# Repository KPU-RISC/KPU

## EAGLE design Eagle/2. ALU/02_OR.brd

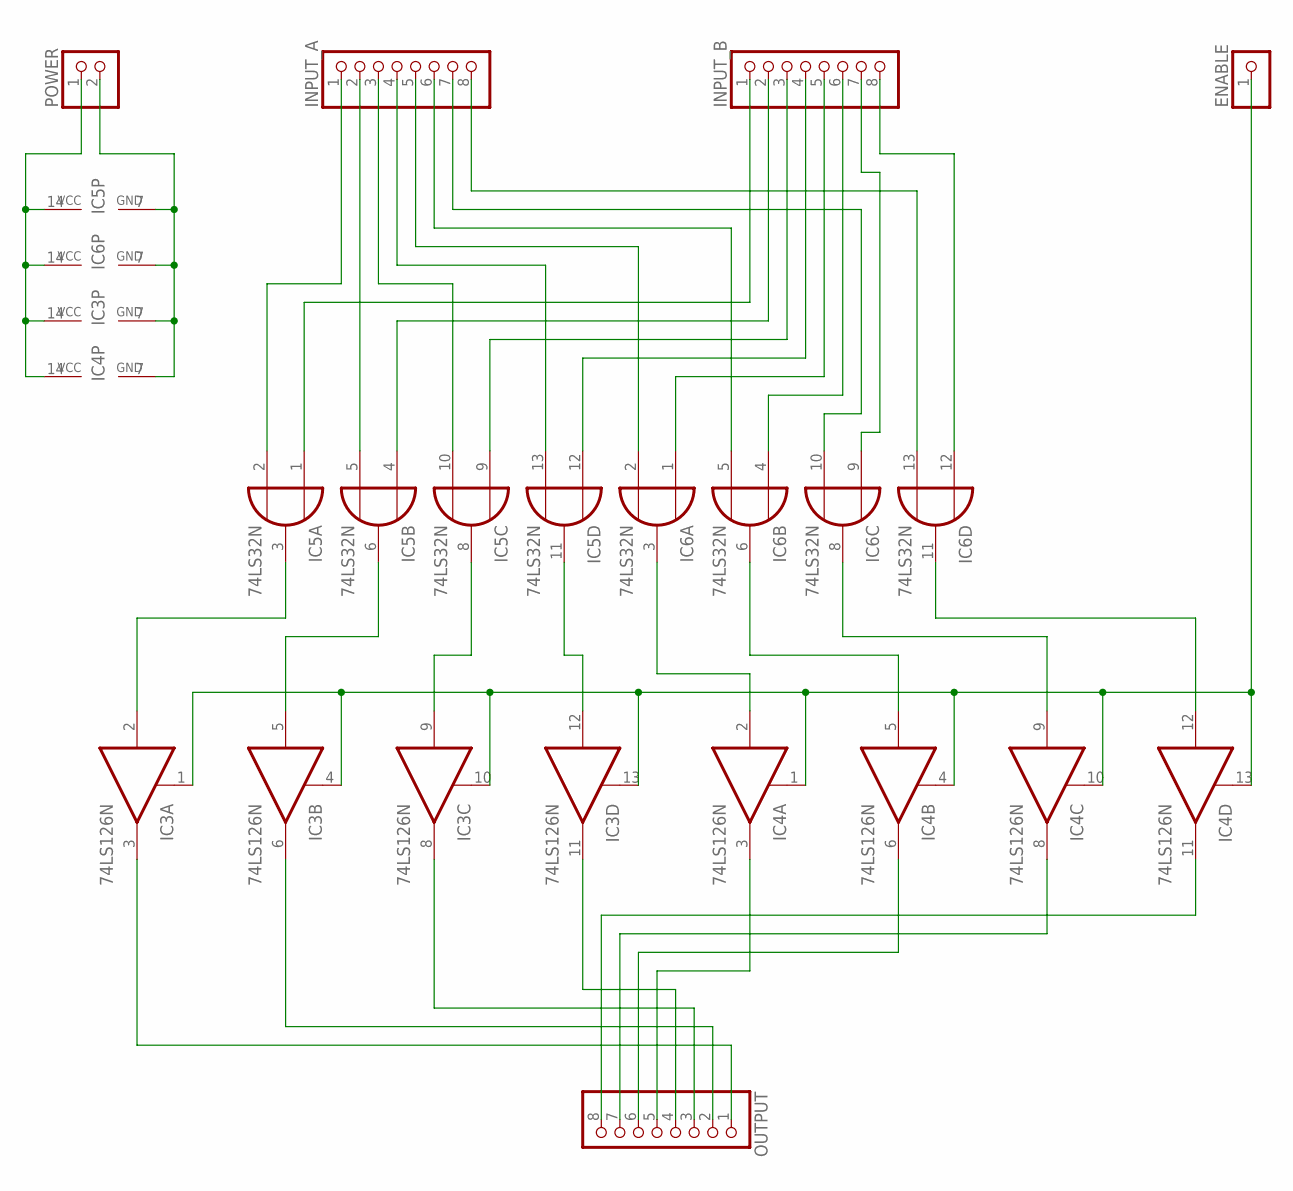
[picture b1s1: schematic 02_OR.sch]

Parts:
ENABLE: PINHD-1X1; 1X01
IC3, IC4: 74LS126N; DIL14
IC5, IC6: 74LS32N; DIL14
INPUT_A: PINHD-1X8; 1X08
INPUT_B: PINHD-1X8; 1X08
OUTPUT: PINHD-1X8; 1X08
POWER: PINHD-1X2; 1X02

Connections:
GND: IC3.7 (GND), IC4.7 (GND), IC5.7 (GND), IC6.7 (GND), POWER.2
unnamed: IC5.2 (I1), INPUT_A.1
unnamed: IC5.1 (I0), INPUT_B.1
unnamed: IC5.5 (I1), INPUT_A.2
unnamed: IC5.4 (I0), INPUT_B.2
unnamed: IC5.10 (I1), INPUT_A.3
unnamed: IC5.9 (I0), INPUT_B.3
unnamed: IC5.13 (I1), INPUT_A.4
unnamed: IC5.12 (I0), INPUT_B.4
unnamed: IC6.2 (I1), INPUT_A.5
unnamed: IC6.1 (I0), INPUT_B.5
unnamed: IC6.5 (I1), INPUT_A.6
unnamed: IC6.4 (I0), INPUT_B.6
unnamed: IC6.10 (I1), INPUT_A.7
unnamed: IC6.9 (I0), INPUT_B.7
unnamed: IC6.13 (I1), INPUT_A.8
unnamed: IC6.12 (I0), INPUT_B.8
unnamed: IC3.5 (I), IC5.6 (O)
unnamed: IC3.9 (I), IC5.8 (O)
unnamed: IC3.12 (I), IC5.11 (O)
unnamed: IC4.2 (I), IC6.3 (O)
unnamed: IC4.5 (I), IC6.6 (O)
unnamed: IC4.9 (I), IC6.8 (O)
unnamed: IC4.12 (I), IC6.11 (O)
unnamed: IC3.3 (O), OUTPUT.1
unnamed: IC3.6 (O), OUTPUT.2
unnamed: IC3.8 (O), OUTPUT.3
unnamed: IC3.11 (O), OUTPUT.4
unnamed: IC4.3 (O), OUTPUT.5
unnamed: IC4.6 (O), OUTPUT.6
unnamed: IC4.8 (O), OUTPUT.7
unnamed: IC4.11 (O), OUTPUT.8
unnamed: ENABLE.1, IC3.1 (OE), IC3.4 (OE), IC3.10 (OE), IC3.13 (OE), IC4.1 (OE), IC4.4 (OE), IC4.10 (OE), IC4.13 (OE)
unnamed: IC3.2 (I), IC5.3 (O)
VCC: IC3.14 (VCC), IC4.14 (VCC), IC5.14 (VCC), IC6.14 (VCC), POWER.1

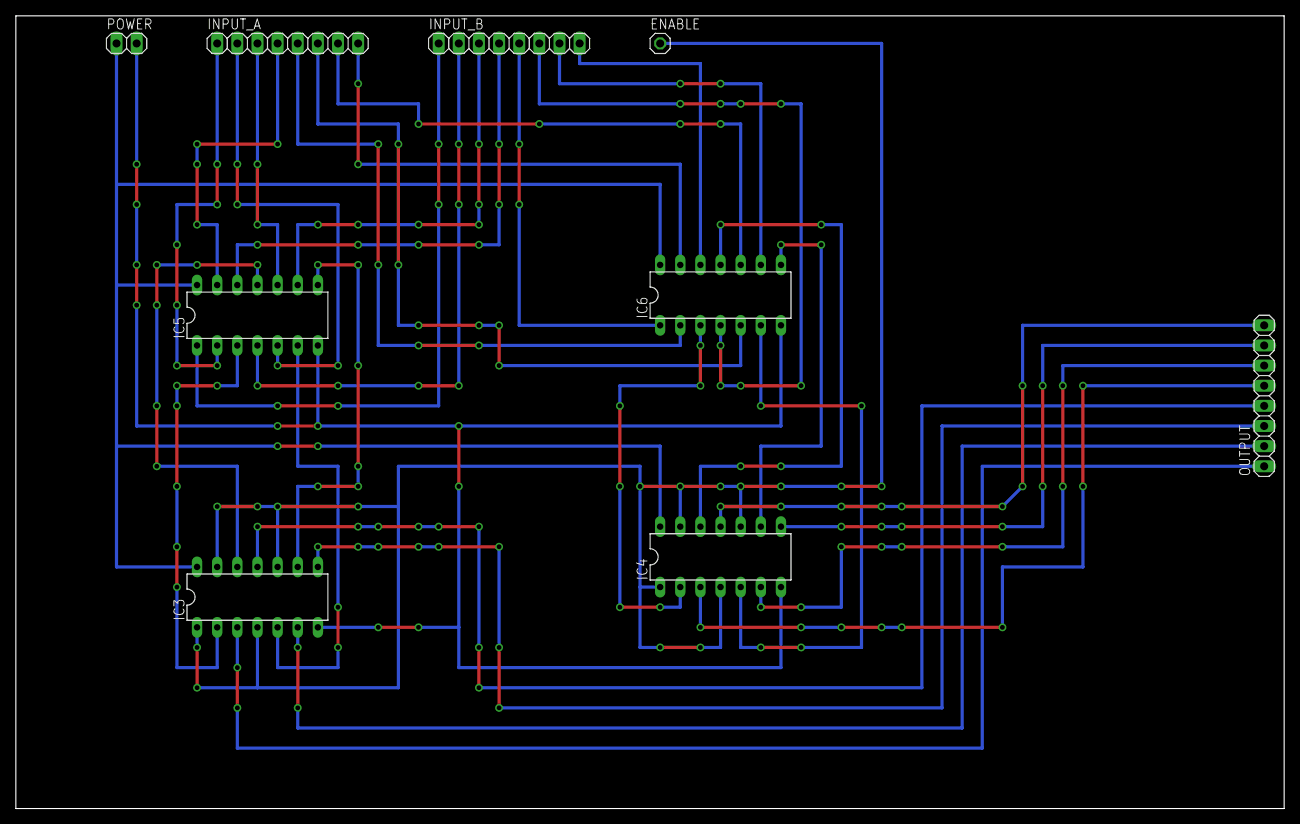
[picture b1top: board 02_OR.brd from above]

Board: 2 copper layers, 160.0 x 100.0 mm, 9 parts (0 on the bottom side), 35 nets.

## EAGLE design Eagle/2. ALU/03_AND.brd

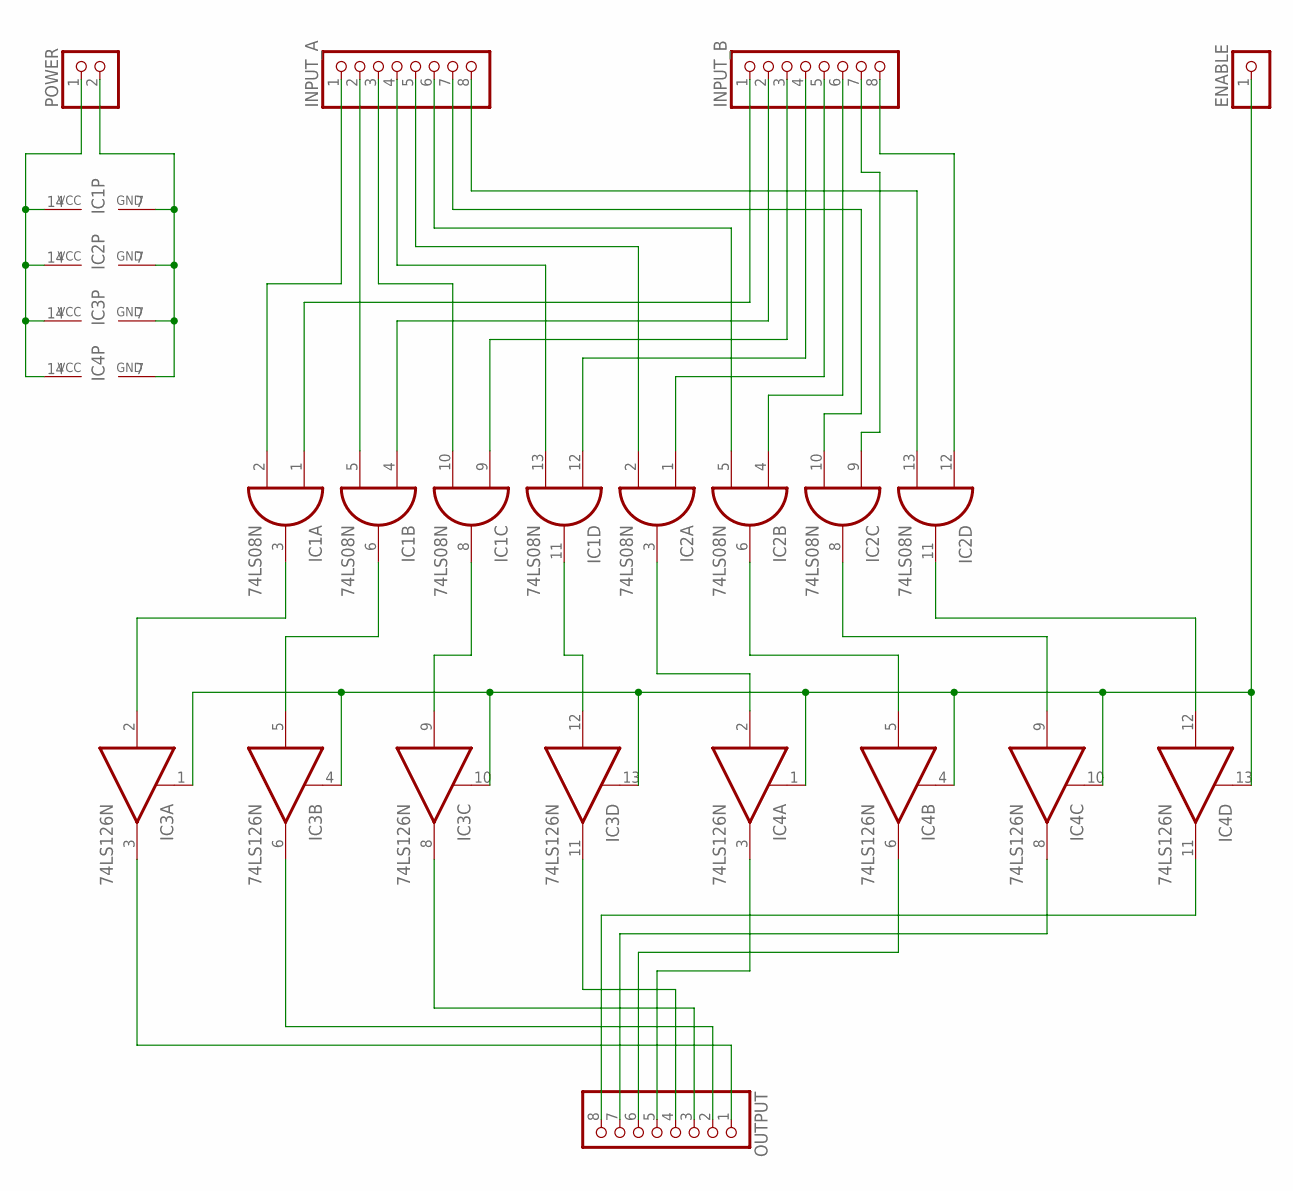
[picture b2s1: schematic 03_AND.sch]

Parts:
ENABLE: PINHD-1X1; 1X01
IC1, IC2: 74LS08N; DIL14
IC3, IC4: 74LS126N; DIL14
INPUT_A: PINHD-1X8; 1X08
INPUT_B: PINHD-1X8; 1X08
OUTPUT: PINHD-1X8; 1X08
POWER: PINHD-1X2; 1X02

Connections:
GND: IC1.7 (GND), IC2.7 (GND), IC3.7 (GND), IC4.7 (GND), POWER.2
unnamed: IC1.2 (I1), INPUT_A.1
unnamed: IC1.1 (I0), INPUT_B.1
unnamed: IC1.5 (I1), INPUT_A.2
unnamed: IC1.4 (I0), INPUT_B.2
unnamed: IC1.10 (I1), INPUT_A.3
unnamed: IC1.9 (I0), INPUT_B.3
unnamed: IC1.13 (I1), INPUT_A.4
unnamed: IC1.12 (I0), INPUT_B.4
unnamed: IC2.2 (I1), INPUT_A.5
unnamed: IC2.1 (I0), INPUT_B.5
unnamed: IC2.5 (I1), INPUT_A.6
unnamed: IC2.4 (I0), INPUT_B.6
unnamed: IC2.10 (I1), INPUT_A.7
unnamed: IC2.9 (I0), INPUT_B.7
unnamed: IC2.13 (I1), INPUT_A.8
unnamed: IC2.12 (I0), INPUT_B.8
unnamed: IC1.6 (O), IC3.5 (I)
unnamed: IC1.8 (O), IC3.9 (I)
unnamed: IC1.11 (O), IC3.12 (I)
unnamed: IC2.3 (O), IC4.2 (I)
unnamed: IC2.6 (O), IC4.5 (I)
unnamed: IC2.8 (O), IC4.9 (I)
unnamed: IC2.11 (O), IC4.12 (I)
unnamed: IC3.3 (O), OUTPUT.1
unnamed: IC3.6 (O), OUTPUT.2
unnamed: IC3.8 (O), OUTPUT.3
unnamed: IC3.11 (O), OUTPUT.4
unnamed: IC4.3 (O), OUTPUT.5
unnamed: IC4.6 (O), OUTPUT.6
unnamed: IC4.8 (O), OUTPUT.7
unnamed: IC4.11 (O), OUTPUT.8
unnamed: ENABLE.1, IC3.1 (OE), IC3.4 (OE), IC3.10 (OE), IC3.13 (OE), IC4.1 (OE), IC4.4 (OE), IC4.10 (OE), IC4.13 (OE)
unnamed: IC1.3 (O), IC3.2 (I)
VCC: IC1.14 (VCC), IC2.14 (VCC), IC3.14 (VCC), IC4.14 (VCC), POWER.1

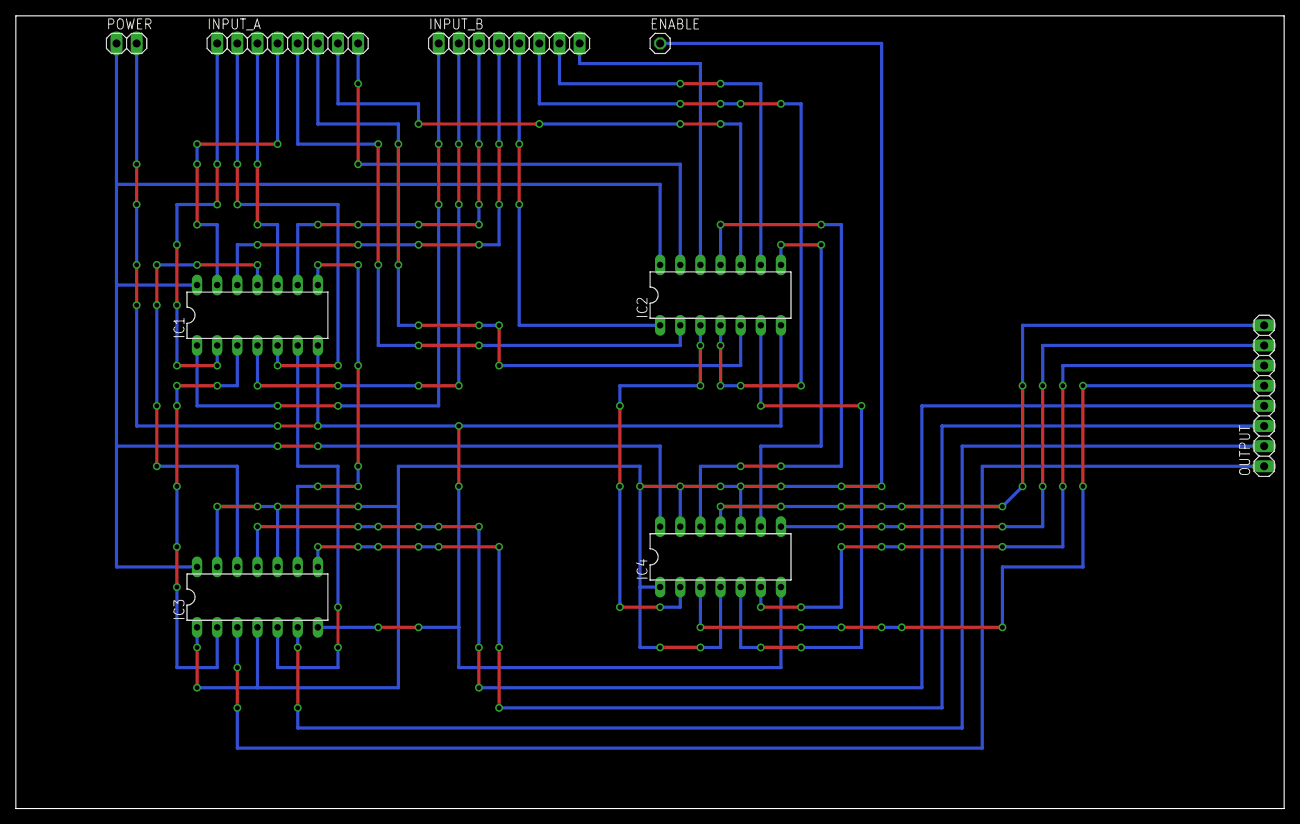
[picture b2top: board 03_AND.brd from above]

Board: 2 copper layers, 160.0 x 100.0 mm, 9 parts (0 on the bottom side), 35 nets.

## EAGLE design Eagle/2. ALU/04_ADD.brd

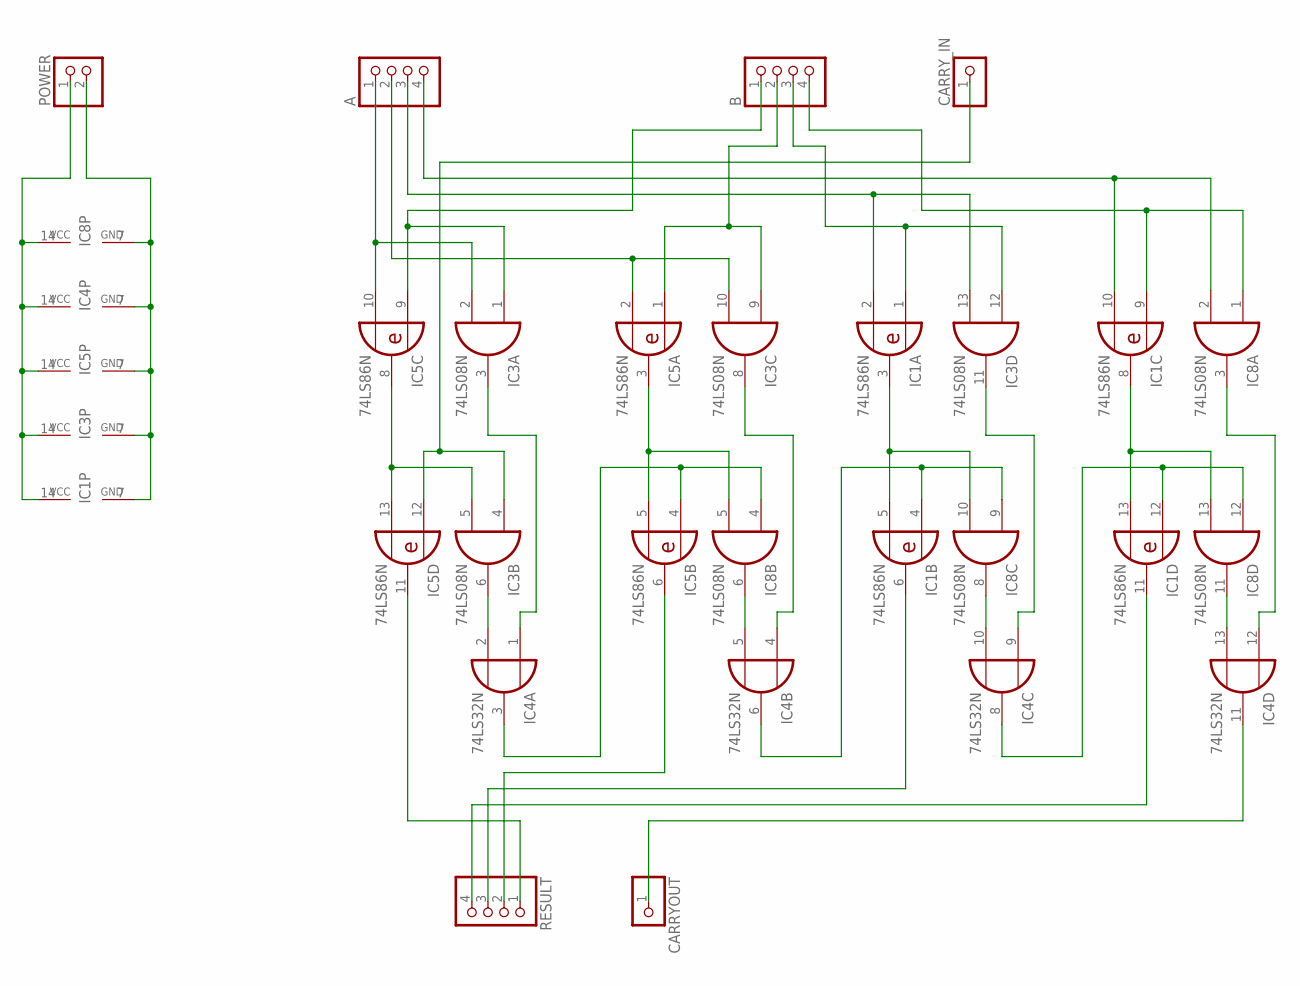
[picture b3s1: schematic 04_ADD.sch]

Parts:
A: PINHD-1X4; 1X04
B: PINHD-1X4; 1X04
CARRYOUT: PINHD-1X1; 1X01
CARRY_IN: PINHD-1X1; 1X01
IC1, IC5: 74LS86N; DIL14
IC3, IC8: 74LS08N; DIL14
IC4: 74LS32N; DIL14
POWER: PINHD-1X2; 1X02
RESULT: PINHD-1X4; 1X04

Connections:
CARRY_OUT: CARRYOUT.1, IC4.11 (O)
GND: IC1.7 (GND), IC3.7 (GND), IC4.7 (GND), IC5.7 (GND), IC8.7 (GND), POWER.2
unnamed: B.1, IC3.1 (I0), IC5.9 (I0)
unnamed: B.3, IC1.1 (I0), IC3.12 (I0)
unnamed: CARRY_IN.1, IC3.4 (I0), IC5.12 (I0)
unnamed: A.1, IC3.2 (I1), IC5.10 (I1)
unnamed: IC3.5 (I1), IC5.8 (O), IC5.13 (I1)
unnamed: IC5.11 (O), RESULT.1
unnamed: IC3.3 (O), IC4.1 (I0)
unnamed: IC3.6 (O), IC4.2 (I1)
unnamed: A.2, IC3.10 (I1), IC5.2 (I1)
unnamed: A.3, IC1.2 (I1), IC3.13 (I1)
unnamed: A.4, IC1.10 (I1), IC8.2 (I1)
unnamed: B.2, IC3.9 (I0), IC5.1 (I0)
unnamed: B.4, IC1.9 (I0), IC8.1 (I0)
unnamed: IC5.3 (O), IC5.5 (I1), IC8.5 (I1)
unnamed: IC1.6 (O), RESULT.3
unnamed: IC1.3 (O), IC1.5 (I1), IC8.10 (I1)
unnamed: IC1.8 (O), IC1.13 (I1), IC8.13 (I1)
unnamed: IC4.3 (O), IC5.4 (I0), IC8.4 (I0)
unnamed: IC5.6 (O), RESULT.2
unnamed: IC1.11 (O), RESULT.4
unnamed: IC4.5 (I1), IC8.6 (O)
unnamed: IC4.10 (I1), IC8.8 (O)
unnamed: IC4.13 (I1), IC8.11 (O)
unnamed: IC3.8 (O), IC4.4 (I0)
unnamed: IC3.11 (O), IC4.9 (I0)
unnamed: IC4.12 (I0), IC8.3 (O)
unnamed: IC1.4 (I0), IC4.6 (O), IC8.9 (I0)
unnamed: IC1.12 (I0), IC4.8 (O), IC8.12 (I0)
VCC: IC1.14 (VCC), IC3.14 (VCC), IC4.14 (VCC), IC5.14 (VCC), IC8.14 (VCC), POWER.1

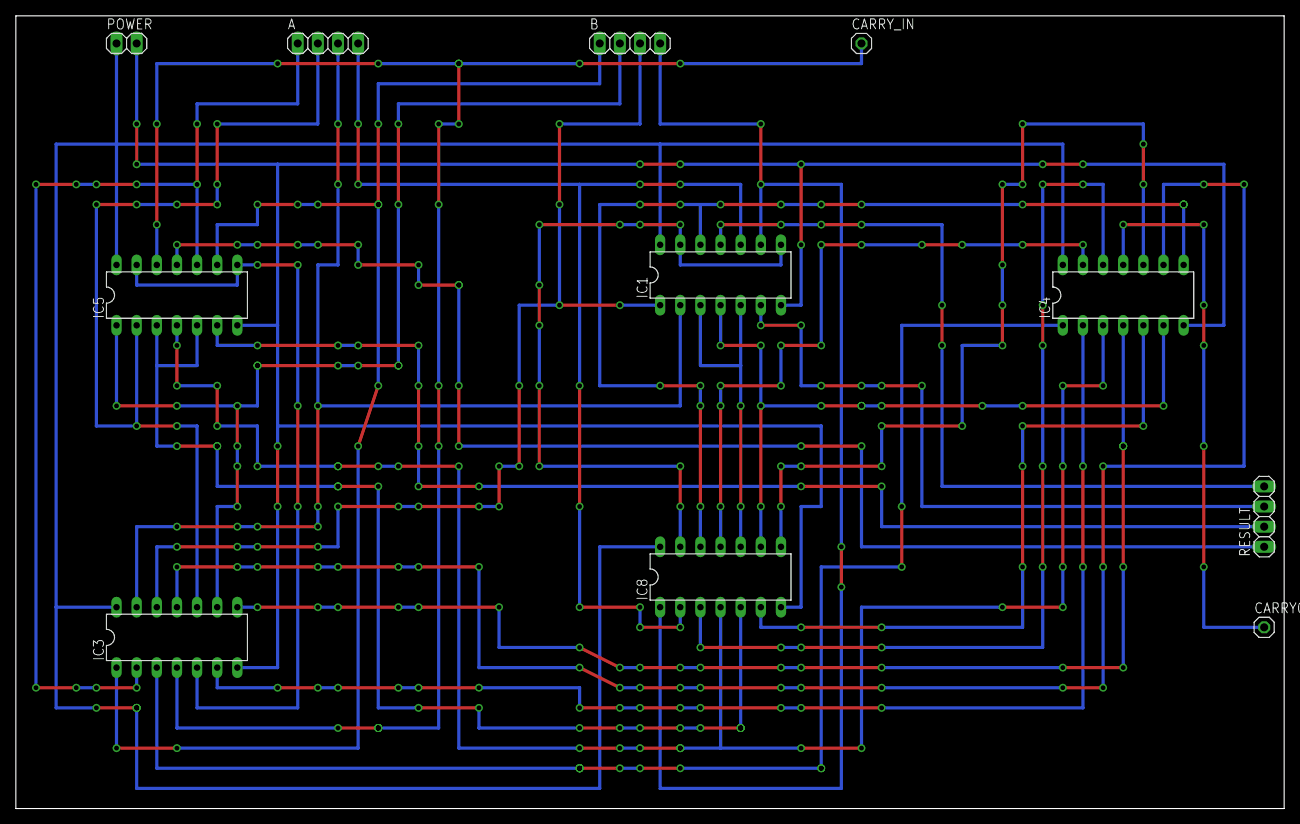
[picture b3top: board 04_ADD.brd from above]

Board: 2 copper layers, 160.0 x 100.0 mm, 11 parts (0 on the bottom side), 31 nets.

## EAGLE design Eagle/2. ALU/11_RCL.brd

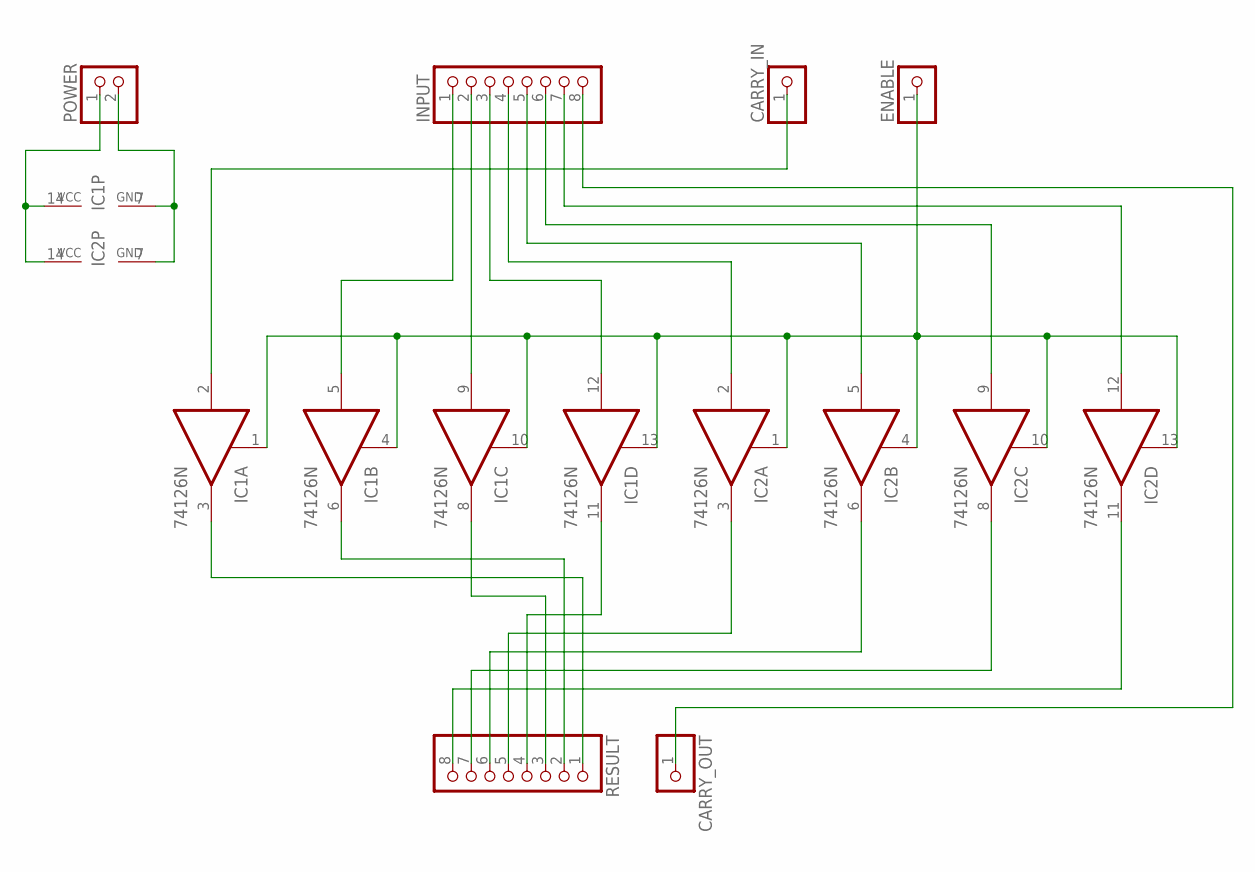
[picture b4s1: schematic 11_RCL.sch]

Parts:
CARRY_IN: PINHD-1X1; 1X01
CARRY_OUT: PINHD-1X1; 1X01
ENABLE: PINHD-1X1; 1X01
IC1, IC2: 74126N; DIL14
INPUT: PINHD-1X8; 1X08
POWER: PINHD-1X2; 1X02
RESULT: PINHD-1X8; 1X08

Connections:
GND: IC1.7 (GND), IC2.7 (GND), POWER.2
unnamed: CARRY_IN.1, IC1.2 (I)
unnamed: IC1.3 (O), RESULT.1
unnamed: IC1.5 (I), INPUT.1
unnamed: IC1.6 (O), RESULT.2
unnamed: IC1.9 (I), INPUT.2
unnamed: IC1.12 (I), INPUT.3
unnamed: IC2.2 (I), INPUT.4
unnamed: IC2.5 (I), INPUT.5
unnamed: IC2.9 (I), INPUT.6
unnamed: IC2.12 (I), INPUT.7
unnamed: IC1.8 (O), RESULT.3
unnamed: IC1.11 (O), RESULT.4
unnamed: IC2.3 (O), RESULT.5
unnamed: IC2.6 (O), RESULT.6
unnamed: IC2.8 (O), RESULT.7
unnamed: IC2.11 (O), RESULT.8
unnamed: CARRY_OUT.1, INPUT.8
unnamed: ENABLE.1, IC1.1 (OE), IC1.4 (OE), IC1.10 (OE), IC1.13 (OE), IC2.1 (OE), IC2.4 (OE), IC2.10 (OE), IC2.13 (OE)
VCC: IC1.14 (VCC), IC2.14 (VCC), POWER.1

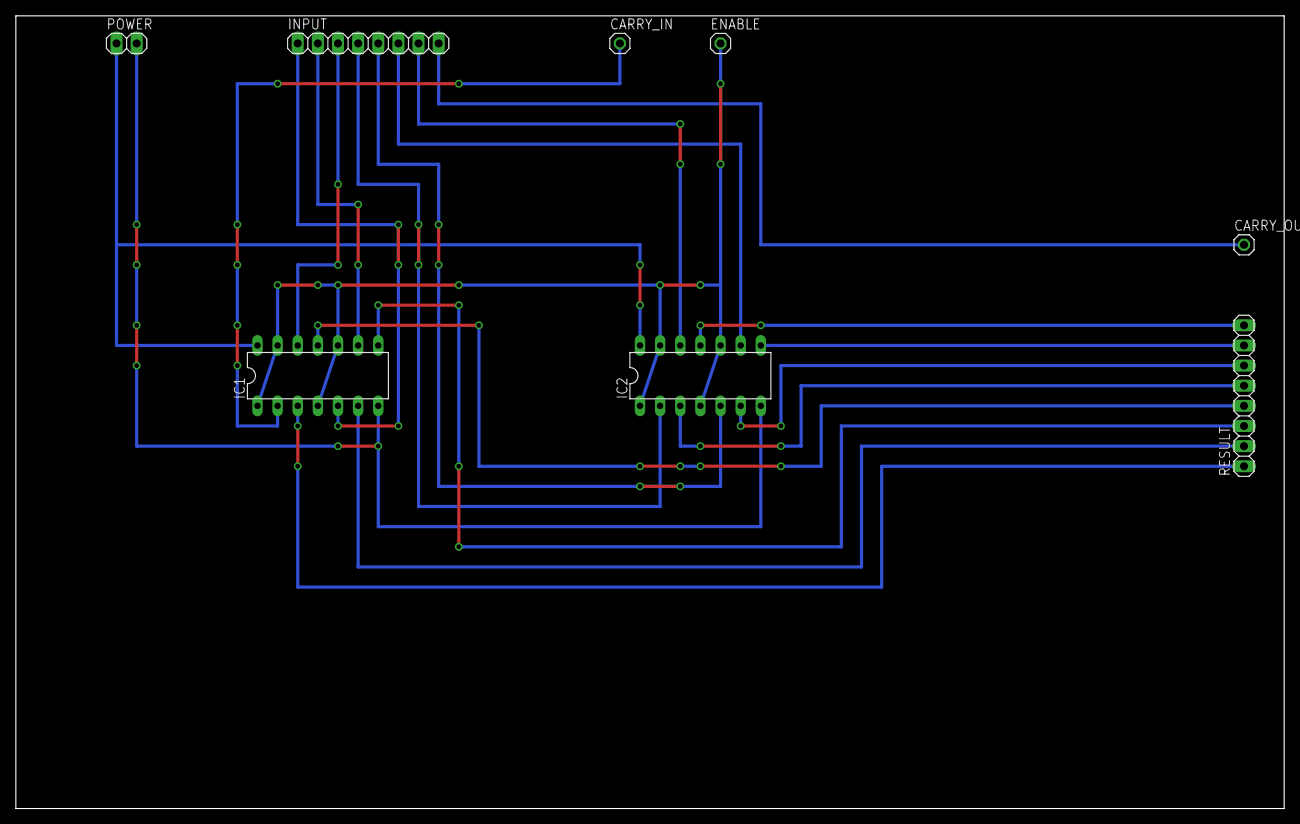
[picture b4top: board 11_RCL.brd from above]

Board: 2 copper layers, 160.0 x 100.0 mm, 8 parts (0 on the bottom side), 20 nets.
